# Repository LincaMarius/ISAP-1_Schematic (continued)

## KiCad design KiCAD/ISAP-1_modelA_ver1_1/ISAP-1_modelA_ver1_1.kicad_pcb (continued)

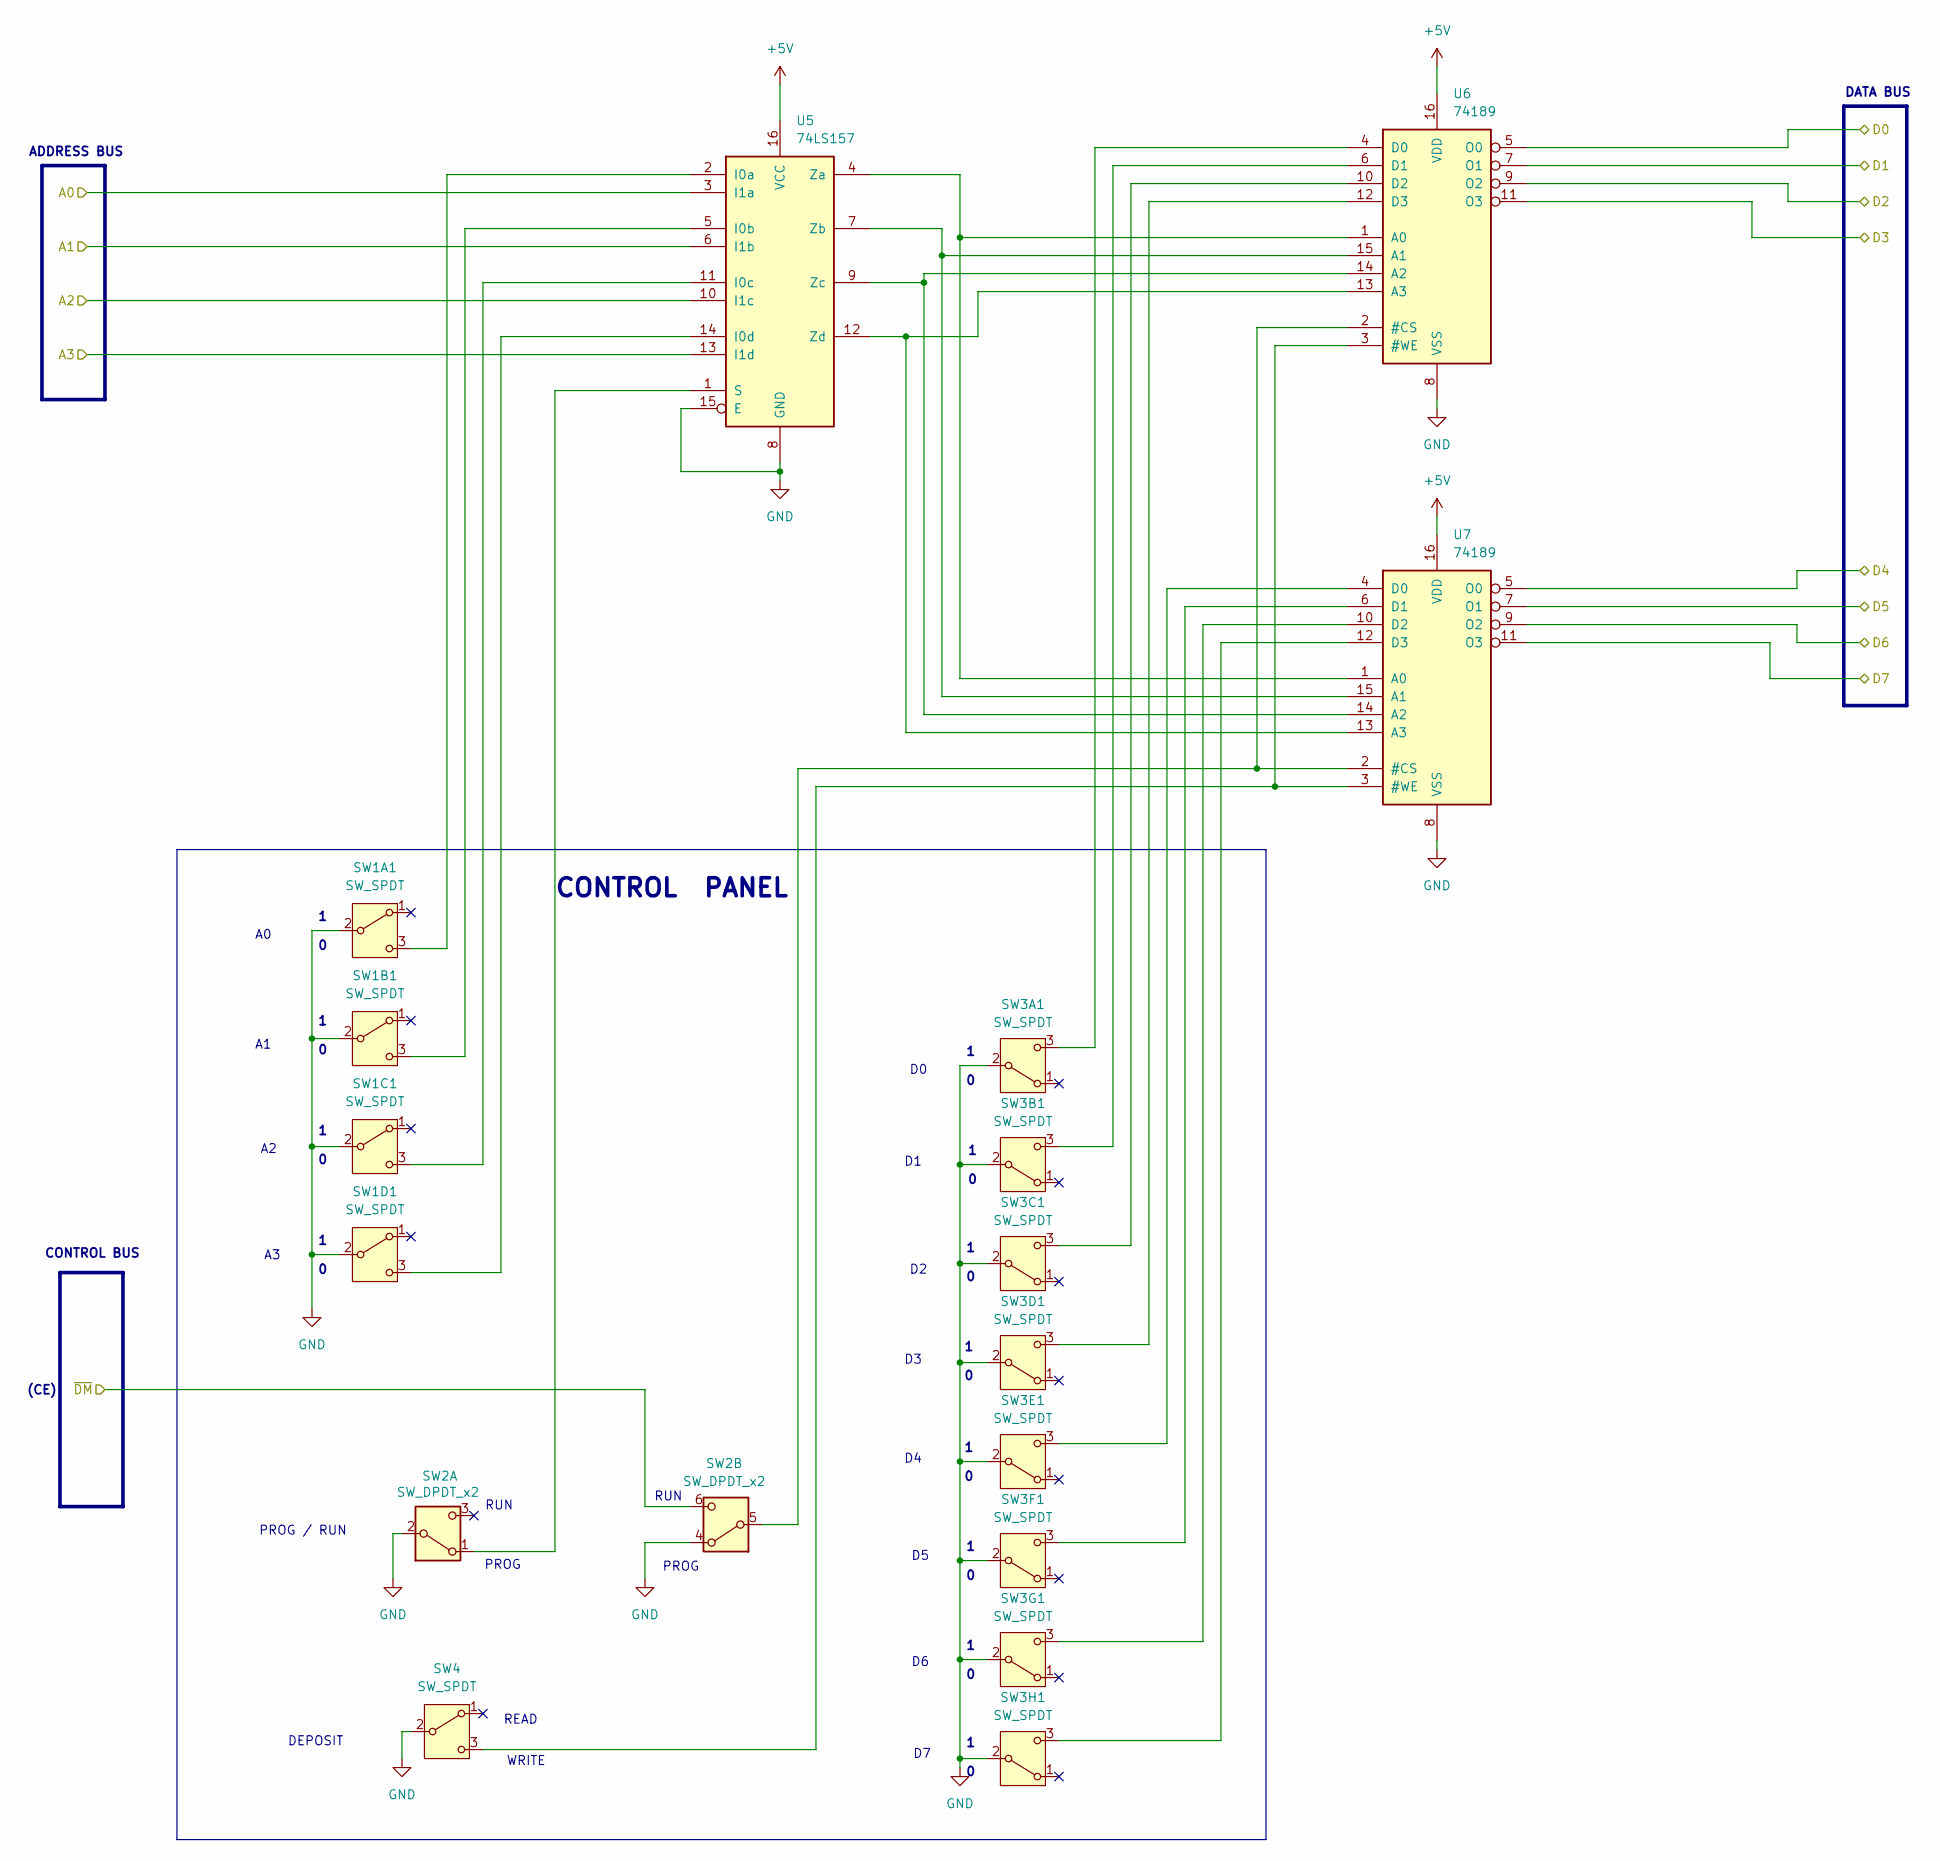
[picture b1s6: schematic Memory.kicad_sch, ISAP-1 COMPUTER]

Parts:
SW1A1, SW1B1, SW1C1, SW1D1, SW3A1, SW3B1, SW3C1, SW3D1, SW3E1, SW3F1, SW3G1, SW3H1, SW4: SW_SPDT; SW_Slide_SPDT_Straight_CK_OS102011MS2Q
SW2: SW_DPDT_x2; SW_CK_JS202011CQN_DPDT_Straight
U5: 74LS157; DIP-16_W7.62mm_LongPads
U6, U7: 74189; DIP-16_W7.62mm_LongPads

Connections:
+5V: U5.16 (VCC), U6.16 (VDD), U7.16 (VDD); also elsewhere on the board
/ALU/D0: U6.5 (O0); also elsewhere on the board
/ALU/D1: U6.7 (O1); also elsewhere on the board
/ALU/D2: U6.9 (O2); also elsewhere on the board
/ALU/D3: U6.11 (O3); also elsewhere on the board
/ALU/D4: U7.5 (O0); also elsewhere on the board
/ALU/D5: U7.7 (O1); also elsewhere on the board
/ALU/D6: U7.9 (O2); also elsewhere on the board
/ALU/D7: U7.11 (O3); also elsewhere on the board
/AddressRegister/A0: U5.3 (I1a); also elsewhere on the board
/AddressRegister/A1: U5.6 (I1b); also elsewhere on the board
/AddressRegister/A2: U5.10 (I1c); also elsewhere on the board
/AddressRegister/A3: U5.13 (I1d); also elsewhere on the board
/~DM: SW2.6 (C)
GND: SW1A1.2 (B), SW1B1.2 (B), SW1C1.2 (B), SW1D1.2 (B), SW2.2 (B), SW2.4 (A), SW3A1.2 (B), SW3B1.2 (B), SW3C1.2 (B), SW3D1.2 (B), SW3E1.2 (B), SW3F1.2 (B), SW3G1.2 (B), SW3H1.2 (B), SW4.2 (B), U5.8 (GND), U5.15 (E), U6.8 (VSS), U7.8 (VSS); also elsewhere on the board
unnamed: SW1A1.3 (C), U5.2 (I0a)
unnamed: SW1B1.3 (C), U5.5 (I0b)
unnamed: SW1C1.3 (C), U5.11 (I0c)
unnamed: SW1D1.3 (C), U5.14 (I0d)
unnamed: SW2.1 (A), U5.1 (S)
unnamed: SW2.5 (B), U6.2 (#CS), U7.2 (#CS)
unnamed: SW3A1.3 (C), U6.4 (D0)
unnamed: SW3B1.3 (C), U6.6 (D1)
unnamed: SW3C1.3 (C), U6.10 (D2)
unnamed: SW3D1.3 (C), U6.12 (D3)
unnamed: SW3E1.3 (C), U7.4 (D0)
unnamed: SW3F1.3 (C), U7.6 (D1)
unnamed: SW3G1.3 (C), U7.10 (D2)
unnamed: SW3H1.3 (C), U7.12 (D3)
unnamed: SW4.3 (C), U6.3 (#WE), U7.3 (#WE)
unnamed: U5.4 (Za), U6.1 (A0), U7.1 (A0)
unnamed: U5.7 (Zb), U6.15 (A1), U7.15 (A1)
unnamed: U5.9 (Zc), U6.14 (A2), U7.14 (A2)
unnamed: U5.12 (Zd), U6.13 (A3), U7.13 (A3)

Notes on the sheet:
1 0
PROG / RUN
READ
PROG
RUN
ADDRESS BUS
CONTROL PANEL
WRITE
DEPOSIT
DATA BUS
(CE)
CONTROL BUS

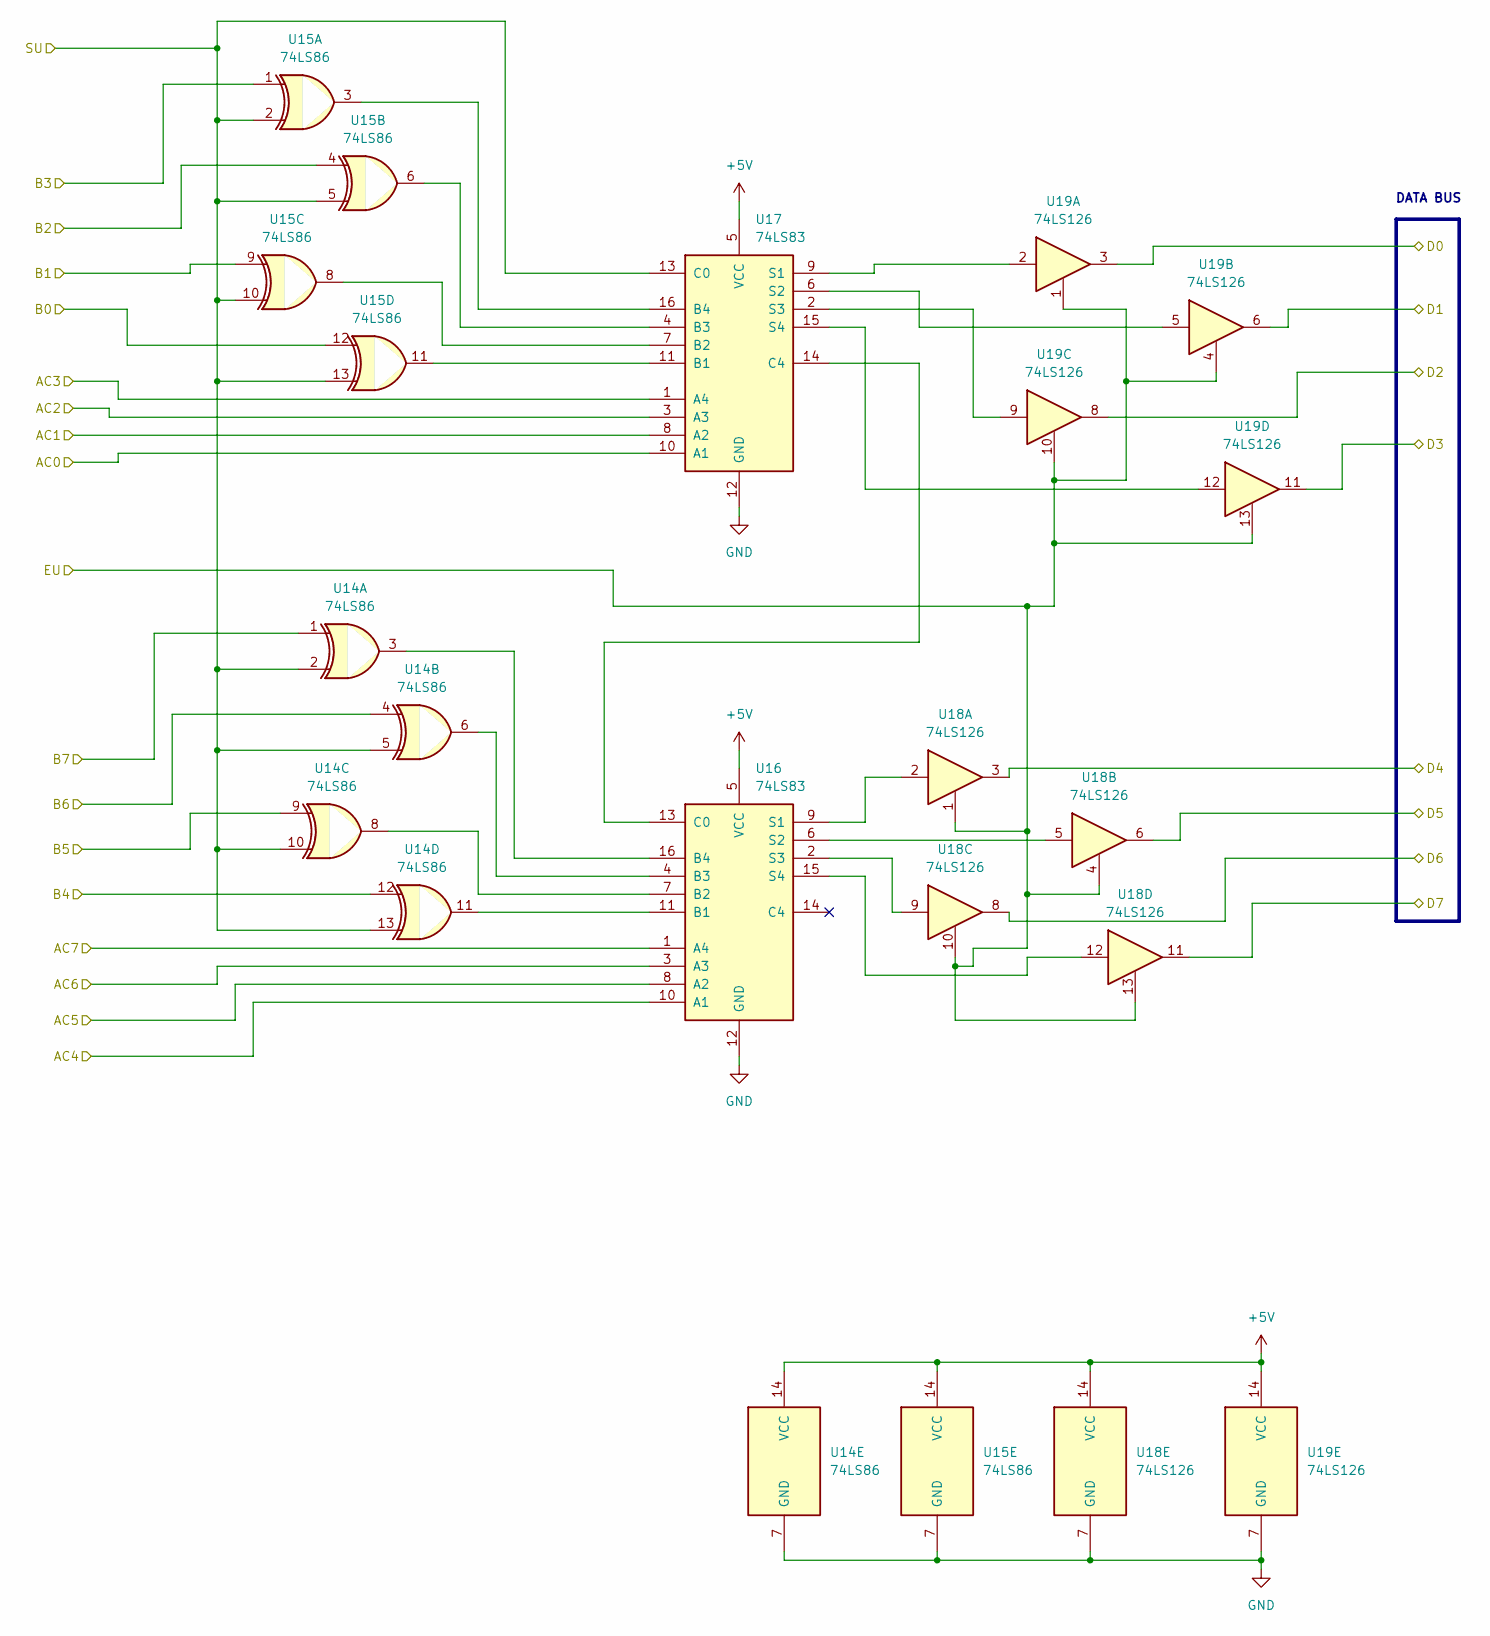
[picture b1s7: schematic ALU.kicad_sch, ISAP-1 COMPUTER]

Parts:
U14, U15: 74LS86; DIP-14_W7.62mm_LongPads
U16, U17: 74LS83; DIP-16_W7.62mm_LongPads
U18, U19: 74LS126; DIP-14_W7.62mm_LongPads

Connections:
+5V: U14.14 (VCC), U15.14 (VCC), U16.5 (VCC), U17.5 (VCC), U18.14 (VCC), U19.14 (VCC); also elsewhere on the board
/ALU/AC0: U17.10 (A1); also elsewhere on the board
/ALU/AC1: U17.8 (A2); also elsewhere on the board
/ALU/AC2: U17.3 (A3); also elsewhere on the board
/ALU/AC4: U16.10 (A1); also elsewhere on the board
/ALU/AC5: U16.8 (A2); also elsewhere on the board
/ALU/AC6: U16.3 (A3); also elsewhere on the board
/ALU/AC7: U16.1 (A4); also elsewhere on the board
/ALU/B0: U15.12; also elsewhere on the board
/ALU/B1: U15.9; also elsewhere on the board
/ALU/B2: U15.4; also elsewhere on the board
/ALU/B3: U15.1; also elsewhere on the board
/ALU/B4: U14.12; also elsewhere on the board
/ALU/B5: U14.9; also elsewhere on the board
/ALU/B6: U14.4; also elsewhere on the board
/ALU/B7: U14.1; also elsewhere on the board
/ALU/D0: U19.3; also elsewhere on the board
/ALU/D1: U19.6; also elsewhere on the board
/ALU/D2: U19.8; also elsewhere on the board
/ALU/D3: U19.11; also elsewhere on the board
/ALU/D4: U18.3; also elsewhere on the board
/ALU/D5: U18.6; also elsewhere on the board
/ALU/D6: U18.8; also elsewhere on the board
/ALU/D7: U18.11; also elsewhere on the board
/EA: U17.1 (A4); also elsewhere on the board
/EU: U18.1, U18.4, U18.10, U18.13, U19.1, U19.4, U19.10, U19.13; also elsewhere on the board
/SU: U14.2, U14.5, U14.10, U14.13, U15.2, U15.5, U15.10, U15.13, U17.13 (C0); also elsewhere on the board
GND: U14.7 (GND), U15.7 (GND), U16.12 (GND), U17.12 (GND), U18.7 (GND), U19.7 (GND); also elsewhere on the board
unnamed: U14.11, U16.11 (B1)
unnamed: U14.8, U16.7 (B2)
unnamed: U14.6, U16.4 (B3)
unnamed: U14.3, U16.16 (B4)
unnamed: U16.13 (C0), U17.14 (C4)
unnamed: U16.9 (S1), U18.2
unnamed: U16.6 (S2), U18.5
unnamed: U16.2 (S3), U18.9
unnamed: U16.15 (S4), U18.12
unnamed: U15.11, U17.11 (B1)
unnamed: U15.8, U17.7 (B2)
unnamed: U15.6, U17.4 (B3)
unnamed: U15.3, U17.16 (B4)
unnamed: U17.9 (S1), U19.2
unnamed: U17.6 (S2), U19.5
unnamed: U17.2 (S3), U19.9
unnamed: U17.15 (S4), U19.12

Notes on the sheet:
DATA BUS

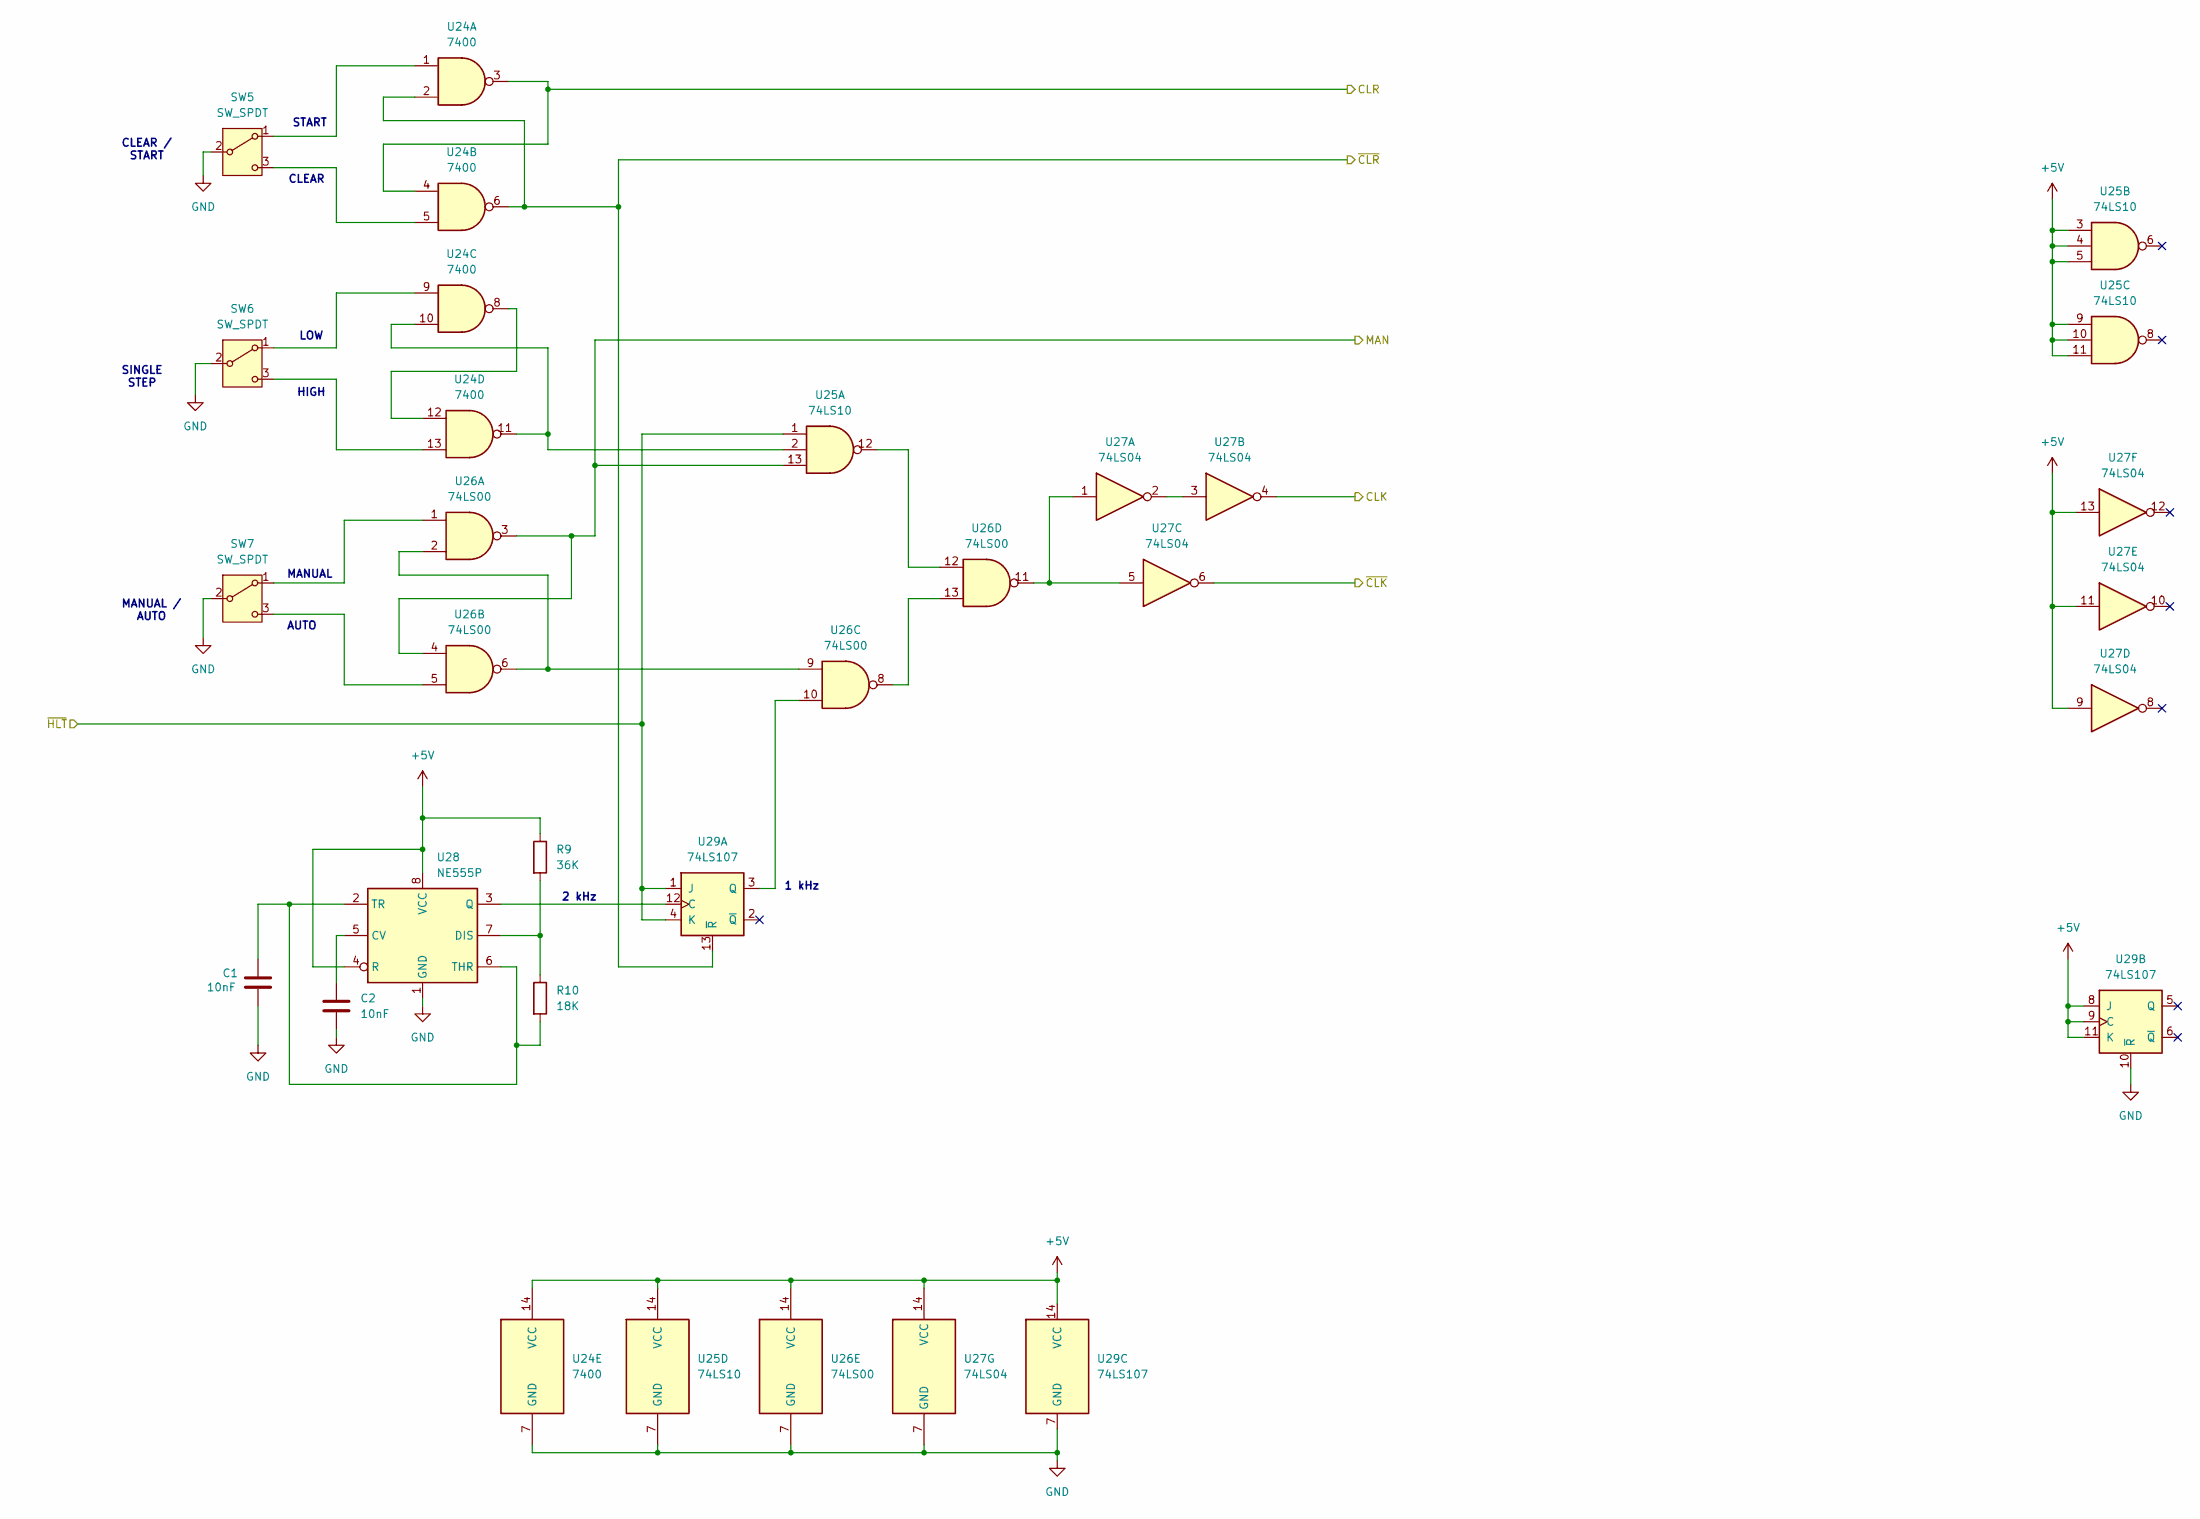
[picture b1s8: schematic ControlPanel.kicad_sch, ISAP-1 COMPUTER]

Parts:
C1, C2: 10nF; C_Disc_D5.0mm_W2.5mm_P5.00mm
R9: 36K; R_Axial_DIN0207_L6.3mm_D2.5mm_P7.62mm_Horizontal
R10: 18K; R_Axial_DIN0207_L6.3mm_D2.5mm_P7.62mm_Horizontal
SW5, SW6, SW7: SW_SPDT; SW_Slide_SPDT_Straight_CK_OS102011MS2Q
U24: 7400; DIP-14_W7.62mm_LongPads
U25: 74LS10; DIP-14_W7.62mm_LongPads
U26: 74LS00; DIP-14_W7.62mm_LongPads
U27: 74LS04; DIP-14_W7.62mm_LongPads
U28: NE555P; DIP-8_W7.62mm
U29: 74LS107; DIP-14_W7.62mm_LongPads

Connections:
+5V: R9.1, U24.14 (VCC), U25.3, U25.4, U25.5, U25.9, U25.10, U25.11, U25.14 (VCC), U26.14 (VCC), U27.9, U27.11, U27.13, U27.14 (VCC), U28.4 (R), U28.8 (VCC), U29.8 (J), U29.9 (C), U29.11 (K), U29.14 (VCC); also elsewhere on the board
/CLK: U27.4; also elsewhere on the board
/CLR: U24.3, U24.4; also elsewhere on the board
/HLT: U25.1, U29.1 (J), U29.4 (K); also elsewhere on the board
/MAN: U25.13, U26.3, U26.4
/~CLK: U27.6; also elsewhere on the board
/~CLR: U24.2, U24.6, U29.13 (~R); also elsewhere on the board
GND: C1.2, C2.2, SW5.2 (B), SW6.2 (B), SW7.2 (B), U24.7 (GND), U25.7 (GND), U26.7 (GND), U27.7 (GND), U28.1 (GND), U29.7 (GND), U29.10 (~R); also elsewhere on the board
unnamed: SW5.1 (A), U24.1
unnamed: SW5.3 (C), U24.5
unnamed: SW6.1 (A), U24.9
unnamed: SW6.3 (C), U24.13
unnamed: SW7.1 (A), U26.1
unnamed: SW7.3 (C), U26.5
unnamed: U24.10, U24.11, U25.2
unnamed: U24.8, U24.12
unnamed: U25.12, U26.12
unnamed: U26.2, U26.6, U26.9
unnamed: U26.11, U27.1, U27.5
unnamed: U26.8, U26.13
unnamed: U27.2, U27.3
unnamed: C2.1, U28.5 (CV)
unnamed: R9.2, R10.1, U28.7 (DIS)
unnamed: U28.3 (Q), U29.12 (C)
unnamed: C1.1, R10.2, U28.2 (TR), U28.6 (THR)
unnamed: U26.10, U29.3 (Q)

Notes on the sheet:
2 kHz
CLEAR
AUTO
MANUAL / AUTO
SINGLE STEP
LOW
MANUAL
1 kHz
HIGH
START
CLEAR / START

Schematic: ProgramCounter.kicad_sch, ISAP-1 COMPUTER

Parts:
U1, U2: 74LS107; DIP-14_W7.62mm_LongPads
U3: 74LS126; DIP-14_W7.62mm_LongPads

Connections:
+5V: U1.14 (VCC), U2.14 (VCC), U3.14 (VCC); also elsewhere on the board
/ALU/D0: U3.11; also elsewhere on the board
/ALU/D1: U3.8; also elsewhere on the board
/ALU/D2: U3.6; also elsewhere on the board
/ALU/D3: U3.3; also elsewhere on the board
/CP: U1.1 (J), U1.4 (K), U1.8 (J), U1.11 (K), U2.1 (J), U2.4 (K), U2.8 (J), U2.11 (K); also elsewhere on the board
/EP: U3.1, U3.4, U3.10, U3.13; also elsewhere on the board
/~CLK: U2.9 (C); also elsewhere on the board
/~CLR: U1.10 (~R), U1.13 (~R), U2.10 (~R), U2.13 (~R); also elsewhere on the board
GND: U1.7 (GND), U2.7 (GND), U3.7 (GND); also elsewhere on the board
unnamed: U1.5 (Q), U1.12 (C), U3.5
unnamed: U1.3 (Q), U3.2
unnamed: U1.9 (C), U2.3 (Q), U3.9
unnamed: U2.5 (Q), U2.12 (C), U3.12

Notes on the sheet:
DATA BUS

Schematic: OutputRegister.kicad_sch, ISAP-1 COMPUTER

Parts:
U22, U23: 74LS173; DIP-16_W7.62mm_LongPads

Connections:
+5V: U22.16 (VCC), U23.16 (VCC); also elsewhere on the board
/ALU/D0: U23.14 (D0); also elsewhere on the board
/ALU/D1: U23.13 (D1); also elsewhere on the board
/ALU/D2: U23.12 (D2); also elsewhere on the board
/ALU/D3: U23.11 (D3); also elsewhere on the board
/ALU/D4: U22.14 (D0); also elsewhere on the board
/ALU/D5: U22.13 (D1); also elsewhere on the board
/ALU/D6: U22.12 (D2); also elsewhere on the board
/ALU/D7: U22.11 (D3); also elsewhere on the board
/BinaryDisplay/DB0: U23.3 (Q0); also elsewhere on the board
/BinaryDisplay/DB1: U23.4 (Q1); also elsewhere on the board
/BinaryDisplay/DB2: U23.5 (Q2); also elsewhere on the board
/BinaryDisplay/DB3: U23.6 (Q3); also elsewhere on the board
/BinaryDisplay/DB4: U22.3 (Q0); also elsewhere on the board
/BinaryDisplay/DB5: U22.4 (Q1); also elsewhere on the board
/BinaryDisplay/DB6: U22.5 (Q2); also elsewhere on the board
/BinaryDisplay/DB7: U22.6 (Q3); also elsewhere on the board
/CLK: U22.7 (Cp), U23.7 (Cp); also elsewhere on the board
/~LO: U22.9 (E1), U22.10 (E2), U23.9 (E1), U23.10 (E2); also elsewhere on the board
GND: U22.1 (Oe1), U22.2 (Oe2), U22.8 (GND), U22.15 (Mr), U23.1 (Oe1), U23.2 (Oe2), U23.8 (GND), U23.15 (Mr); also elsewhere on the board

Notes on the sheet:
(I/O)

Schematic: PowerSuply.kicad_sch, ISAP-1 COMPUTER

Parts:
C3: 1000uF; CP_Radial_D10.0mm_P5.00mm
C4: 220uF; CP_Radial_D5.0mm_P2.00mm
D9, D10, D11, D12: 1N4001; D_DO-41_SOD81_P10.16mm_Horizontal
F1: 3/8A (0.4A); Fuseholder_Clip-5x20mm_Schurter_CQM_Inline_P20.60x5.00mm_D1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
HS1: Heatsink; Heatsink_AAVID_590302B03600G
P1: IEC_60320_C13_Plug; SolderWire-1.5sqmm_1x03_P6mm_D1.7mm_OD3mm
T1: F-25X 115V(240V) /12V 1.5A; Transformer_CHK_EI54-16VA_Neutral
U30: LM340T-5; TO-220-3_Vertical

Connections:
+5V: C4.1, U30.3 (VO); also elsewhere on the board
GND: C3.2, C4.2, D10.2 (A), D12.2 (A), U30.2 (GND); also elsewhere on the board
unnamed: D9.2 (A), D10.1 (K), T1.4 (SB)
unnamed: D11.2 (A), D12.1 (K), T1.3 (SA)
unnamed: C3.1, D9.1 (K), D11.1 (K), U30.1 (VI)
unnamed: F1.1, P1.2 (L)
unnamed: P1.1 (N), T1.2 (AB)
unnamed: F1.2, T1.1 (AA)

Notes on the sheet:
Transformer 18 VA
Max 1.5A
15.37V
MAIN 115 VAC or 240 VAC

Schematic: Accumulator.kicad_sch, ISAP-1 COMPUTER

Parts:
U10, U11: 74LS173; DIP-16_W7.62mm_LongPads
U12, U13: 74LS126; DIP-14_W7.62mm_LongPads

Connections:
+5V: U10.16 (VCC), U11.16 (VCC), U12.14 (VCC), U13.14 (VCC); also elsewhere on the board
/ALU/AC0: U11.3 (Q0), U12.2; also elsewhere on the board
/ALU/AC1: U11.4 (Q1), U12.5; also elsewhere on the board
/ALU/AC2: U11.5 (Q2), U12.9; also elsewhere on the board
/ALU/AC4: U10.3 (Q0), U13.2; also elsewhere on the board
/ALU/AC5: U10.4 (Q1), U13.5; also elsewhere on the board
/ALU/AC6: U10.5 (Q2), U13.9; also elsewhere on the board
/ALU/AC7: U10.6 (Q3), U13.12; also elsewhere on the board
/ALU/D0: U11.14 (D0), U12.3; also elsewhere on the board
/ALU/D1: U11.13 (D1), U12.6; also elsewhere on the board
/ALU/D2: U11.12 (D2), U12.8; also elsewhere on the board
/ALU/D3: U11.11 (D3), U12.11; also elsewhere on the board
/ALU/D4: U10.14 (D0), U13.3; also elsewhere on the board
/ALU/D5: U10.13 (D1), U13.6; also elsewhere on the board
/ALU/D6: U10.12 (D2), U13.8; also elsewhere on the board
/ALU/D7: U10.11 (D3), U13.11; also elsewhere on the board
/CLK: U10.7 (Cp), U11.7 (Cp); also elsewhere on the board
/EA: U11.6 (Q3), U12.1, U12.4, U12.10, U12.12, U12.13, U13.1, U13.4, U13.10, U13.13; also elsewhere on the board
/~LA: U10.9 (E1), U10.10 (E2), U11.9 (E1), U11.10 (E2); also elsewhere on the board
GND: U10.1 (Oe1), U10.2 (Oe2), U10.8 (GND), U10.15 (Mr), U11.1 (Oe1), U11.2 (Oe2), U11.8 (GND), U11.15 (Mr), U12.7 (GND), U13.7 (GND); also elsewhere on the board

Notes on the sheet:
DATA BUS

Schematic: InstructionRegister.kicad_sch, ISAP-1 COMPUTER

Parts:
U8, U9: 74LS173; DIP-16_W7.62mm_LongPads

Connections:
+5V: U8.16 (VCC), U9.16 (VCC); also elsewhere on the board
/ALU/D0: U9.3 (Q0), U9.14 (D0); also elsewhere on the board
/ALU/D1: U9.4 (Q1), U9.13 (D1); also elsewhere on the board
/ALU/D2: U9.5 (Q2), U9.12 (D2); also elsewhere on the board
/ALU/D3: U9.6 (Q3), U9.11 (D3); also elsewhere on the board
/ALU/D4: U8.14 (D0); also elsewhere on the board
/ALU/D5: U8.13 (D1); also elsewhere on the board
/ALU/D6: U8.12 (D2); also elsewhere on the board
/ALU/D7: U8.11 (D3); also elsewhere on the board
/CLK: U8.7 (Cp), U9.7 (Cp); also elsewhere on the board
/CLR: U8.15 (Mr); also elsewhere on the board
/ControlUnit/I4: U8.3 (Q0); also elsewhere on the board
/ControlUnit/I5: U8.4 (Q1); also elsewhere on the board
/ControlUnit/I6: U8.5 (Q2); also elsewhere on the board
/ControlUnit/I7: U8.6 (Q3); also elsewhere on the board
/~EI: U9.1 (Oe1), U9.2 (Oe2); also elsewhere on the board
/~LI: U8.9 (E1), U8.10 (E2), U9.9 (E1), U9.10 (E2); also elsewhere on the board
GND: U8.1 (Oe1), U8.2 (Oe2), U8.8 (GND), U9.8 (GND), U9.15 (Mr); also elsewhere on the board

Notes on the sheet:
DATA BUS

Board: 2 copper layers, 96 parts (0 on the bottom side), 191 nets, no tracks yet.

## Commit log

2024-11-27 modified: README.md
2024-11-27 new file: Pictures/Figure1.png modified: README.md
2024-11-27 new file: Pictures/Figure2.png modified: README.md
2024-11-27 new file: Pictures/Figure3.png modified: README.md
2024-11-27 new file: Pictures/Figure4.png modified: README.md
2024-11-27 new file: Pictures/Figure5.png modified: README.md
2024-11-27 modified: Pictures/Figure5.png modified: README.md
2024-11-27 new file: Pictures/Figure6.png
2024-11-28 new file: Pictures/Figure7.png modified: README.md
2024-11-28 modified: Pictures/Figure5.png modified: Pictures/Figure6.png modified: README.md
2024-11-28 modified: Pictures/Figure6.png modified: Pictures/Figure7.png modified: README.md
2024-11-28 new file: Pictures/Figure8.png modified: README.md
2024-11-28 new file: Pictures/Figure9.png modified: README.md
2024-11-28 modified: Pictures/Figure9.png
2024-11-28 new file: Pictures/Figure10.png modified: README.md
2024-11-28 new file: Pictures/Figure11.png modified: README.md
2024-11-28 modified: Pictures/Figure5.png
2024-11-28 modified: Pictures/Figure6.png
2024-11-28 modified: Pictures/Figure10.png modified: Pictures/Figure5.png modified: Pictures/Figure9.png
2024-11-28 modified: Pictures/Figure10.png modified: Pictures/Figure11.png new file: Pictures/Figure12.png modified: README.md
2024-11-30 modified: Pictures/Figure9.png modified: README.md
2024-11-30 modified: Pictures/Figure3.png modified: README.md
2024-11-30 modified: Pictures/Figure4.png modified: README.md
2024-11-30 new file: Pictures/Figure13.png modified: README.md
2024-11-30 modified: Pictures/Figure13.png new file: Pictures/Figure14.png new file: Pictures/Figure15.png modified: README.md
2024-11-30 new file: Pictures/Figure16.png modified: README.md
2024-11-30 new file: Pictures/Figure17.png modified: README.md
2024-11-30 new file: Pictures/Figure18.png modified: README.md
2024-11-30 new file: Pictures/Figure19.png new file: Pictures/Figure20.png modified: README.md
2024-11-30 new file: KiCAD/ISAP-1 ver1/ALU.kicad_sch
2024-12-04 modified: Pictures/Figure3.png
2024-12-04 modified: Pictures/Figure6.png modified: README.md
2024-12-04 modified: Pictures/Figure7.png modified: README.md
2024-12-04 modified: Pictures/Figure8.png modified: README.md
2024-12-04 modified: README.md modified: Pictures/Figure10.png
2024-12-04 modified: Pictures/Figure10.png
2024-12-04 modified: Pictures/Figure11.png modified: README.md
2024-12-04 modified: Pictures/Figure12.png modified: README.md
2024-12-04 modified: Pictures/Figure13.png modified: README.md
2024-12-04 modified: Pictures/Figure14.png modified: README.md
2024-12-04 modified: Pictures/Figure15.png deleted: Pictures/Figure16.png deleted: Pictures/Figure17.png deleted: Pictures/Figure18.png deleted: Pictures/Figure19.png deleted: Pictures/Figure20.png modified: RE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
2024-12-05 new file: Pictures/Figure18.png
2024-12-05 deleted: KiCAD/ISAP-1 ver1/ALU.kicad_sch
2024-12-05 new file: KiCAD/ISAP-1_ver1/ALU.kicad_sch
2024-12-06 new file: Pictures/Figure19.png modified: README.md
2024-12-06 new file: Pictures/Figure20.png modified: README.md
2024-12-06 renamed: KiCAD/ISAP-1_ver1/ALU.kicad_sch -> KiCAD/ISAP-1_revA_ver1/ALU.kicad_sch
2024-12-06 new file: KiCAD/ISAP-1_revB_ver1/ALU.kicad_sch
2024-12-06 deleted: KiCAD/ISAP-1_revB_ver1/ISAP-1_revB_ver1-backups/ISAP-1_revB_ver1-2024-12-06_040022.zip
2025-01-19 modified: Pictures/Figure19.png
2025-01-19 new file: KiCAD/ISAP-1_modelA_ver1_1/ALU.kicad_sch
2025-01-22 modified: Pictures/Figure8.png
2025-01-22 modified: Pictures/Figure14.png
2025-01-22 modified: Pictures/Figure15.png
2025-01-22 modified: Pictures/Figure16.png
2025-01-22 modified: Pictures/Figure18.png
2025-01-22 new file: KiCAD/ISAP-1_modelA_ver1_0.zip
2025-01-22 modified: Pictures/Figure20.png
2025-01-22 modified: Pictures/Figure21.png new file: Pictures/Figure22.png
2025-01-22 new file: KiCAD/ISAP-1_modelA_ver1_1.zip
2025-01-23 modified: KiCAD/ISAP-1_modelA_ver1_0.zip
2025-01-23 modified: KiCAD/ISAP-1_modelA_ver1_1.zip
2025-01-24 new file: Pictures/Figure23.png
2025-01-24 new file: Pictures/Figure24.png
2025-01-24 new file: KiCAD/ISAP-1_modelB_ver1_0.zip new file: Pictures/Figure25.png
2025-01-25 new file: Pictures/Figure26.png
2025-01-25 new file: Pictures/Figure27.png
2025-01-25 new file: Pictures/Figure28.png
2025-01-25 new file: KiCAD/ISAP-1_modelB_ver1_1.zip
2025-01-27 new file: Pictures/Figure29.png
2025-01-27 new file: Pictures/Figure30.png
2025-01-27 new file: Pictures/Figure31.png
2025-01-27 new file: Pictures/Figure32.png
2025-01-27 new file: Pictures/Figure33.png
2025-01-27 new file: Pictures/Figure34.png
2025-01-27 new file: Pictures/Figure35.png
2025-01-31 modified: Pictures/Figure29.png
2025-01-31 modified: Pictures/Figure30.png
2025-01-31 modified: Pictures/Figure31.png
2025-01-31 modified: Pictures/Figure32.png
2025-01-31 modified: Pictures/Figure35.png
2025-01-31 new file: Pictures/Figure36.png
2025-01-31 new file: Pictures/Figure37.png
2025-01-31 new file: Pictures/Figure38.png
2025-01-31 new file: Pictures/Figure39.png
2025-01-31 new file: Pictures/Figure40.png
2025-01-31 new file: Pictures/Figure41.png
2025-01-31 modified: Pictures/Figure41.png
2025-01-31 new file: Pictures/Figure42.png
2025-01-31 new file: Pictures/Figure43.png
2025-01-31 new file: Pictures/Figure44.png
2025-01-31 new file: Pictures/Figure45.png
2025-01-31 new file: Pictures/Figure46.png
2025-01-31 new file: Pictures/Figure47.png
2025-01-31 new file: Pictures/Figure48.png
2025-01-31 new file: Pictures/Figure49.png
2025-01-31 new file: Pictures/Figure50.png
2025-01-31 new file: Pictures/Figure51.png
2025-01-31 new file: Pictures/Figure52.png
2025-01-31 new file: Pictures/Figure53.png
2025-01-31 new file: Pictures/Figure54.png
2025-01-31 new file: KiCAD/ISAP-1_modelB_ver1_2.zip
2025-03-16 modified: Pictures/Figure1.png
2025-03-17 modified: Pictures/Figure2.png new file: Pictures/Figure2b.png
2025-03-17 deleted: Pictures/Figure2b.png modified: Pictures/Figure3.png new file: Pictures/Figure3b.png
2025-03-17 deleted: Pictures/Figure3b.png modified: Pictures/Figure4.png new file: Pictures/Figure4b.png
2025-03-17 deleted: Pictures/Figure4b.png modified: Pictures/Figure5.png new file: Pictures/Figure5b.png
2025-04-16 modified: Pictures/Figure2.png
2025-04-16 modified: Pictures/Figure4.png
2025-04-17 modified: Pictures/Figure7.png
2025-04-17 modified: Pictures/Figure11.png
2025-04-17 modified: Pictures/Figure12.png
2025-04-17 modified: Pictures/Figure13.png
2025-04-17 modified: Pictures/Figure17.png
2025-04-19 new file: Pictures/Figure8b.png
2025-04-19 new file: Pictures/Figure8c.png
2025-04-19 new file: Pictures/Figure14b.png
2025-04-19 new file: Pictures/Figure14c.png
2025-04-19 new file: Pictures/Figure15b.png
2025-04-19 new file: Pictures/Figure15c.png
2025-04-20 modified: Pictures/Figure8b.png
2025-04-20 modified: Pictures/Figure8c.png
2025-04-20 new file: Pictures/Figure16b.png
2025-04-20 new file: Pictures/Figure16c.png
2025-04-20 new file: Pictures/Figure17b.png
2025-04-20 new file: Pictures/Figure17c.png
2025-04-21 modified: Pictures/Figure16b.png
2025-04-21 modified: Pictures/Figure16c.png
2025-04-21 new file: Pictures/Figure18b.png
2025-04-21 new file: Pictures/Figure18c.png
2025-04-21 new file: Pictures/Figure19b.png
2025-04-21 new file: Pictures/Figure19c.png
2025-04-21 modified: Pictures/Figure21.png
2025-04-21 modified: Pictures/Figure22.png
2025-04-21 modified: Pictures/Figure23.png
2025-04-21 modified: Pictures/Figure24.png
2025-04-21 new file: KiCAD/ISAP-1_TTL_ver1_0.zip
2025-06-21 new file: Pictures/Figure17.png
2025-06-21 modified: Pictures/Figure19.png modified: Pictures/Figure20.png
2025-06-21 new file: Pictures/Figure21.png
2025-06-21 new file: KiCAD/ISAP1_TTL_SBC_ver1_0.zip
2025-08-19 deleted: Pictures/Figure1.png
2025-08-19 modified: Pictures/Figure50.png
2025-08-20 modified: Pictures/Figure51.png
2025-08-20 modified: Pictures/Figure52.png
2025-08-20 modified: Pictures/Figure53.png
2025-08-20 modified: Pictures/Figure54.png
2025-08-20 new file: Pictures/Figure55.png
2025-08-20 new file: Pictures/Figure56.png
2025-08-20 new file: Pictures/Figure57.png
2025-08-20 new file: Pictures/Figure58.png
2025-08-21 new file: KiCAD/ISAP-1_TTL_CPU_1_0.zip
